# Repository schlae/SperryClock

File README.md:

# Nine Digit Sperry Neon Display Clock

Here's a cute little clock I designed that uses a Sperry neon display -- sometimes known as a Panaplex display. Please note this is not a fully completed project. Although I fabbed out boards and got the display working, I never got around to finishing the firmware.

The particular display in this clock is a Sperry SP-425-09, but the basic design will probably work with other Panaplex displays as well.

The brains of the operation is an ATMega328P with a 16MHz crystal. You can load it with the Arduino bootloader and write programs for it using the Arduino IDE, or you can program it directly using avr-gcc, AVR Libc, and avrdude.

[Here is the schematic.](https://github.com/schlae/SperryClock/blob/main/NineDigit.pdf)

The basic design uses 9 transistors to multiplex the segment signals to each of the digits in the display. Typical Panaplex displays must be multiplexed otherwise the segment cathode material will start to plate out and darken the display, so avoid operating the display with just a single digit turned on continuously.

The [firmware](https://github.com/schlae/SperryClock/blob/main/NineDigit.ino) is incomplete but does include all the code required to drive the multiplexed display.

Still to be done:

* Driver for the DS3231
* Button handling
* Clock logic 

## Fabrication and Assembly Notes
This is a two-layer board, outer dimensions of 115mm x 50mm. 

The Sperry display should be installed in a socket. I've specified a part from EDAC but you might be able to find a cheaper one. The pin spacing is 0.156" (3.96mm).

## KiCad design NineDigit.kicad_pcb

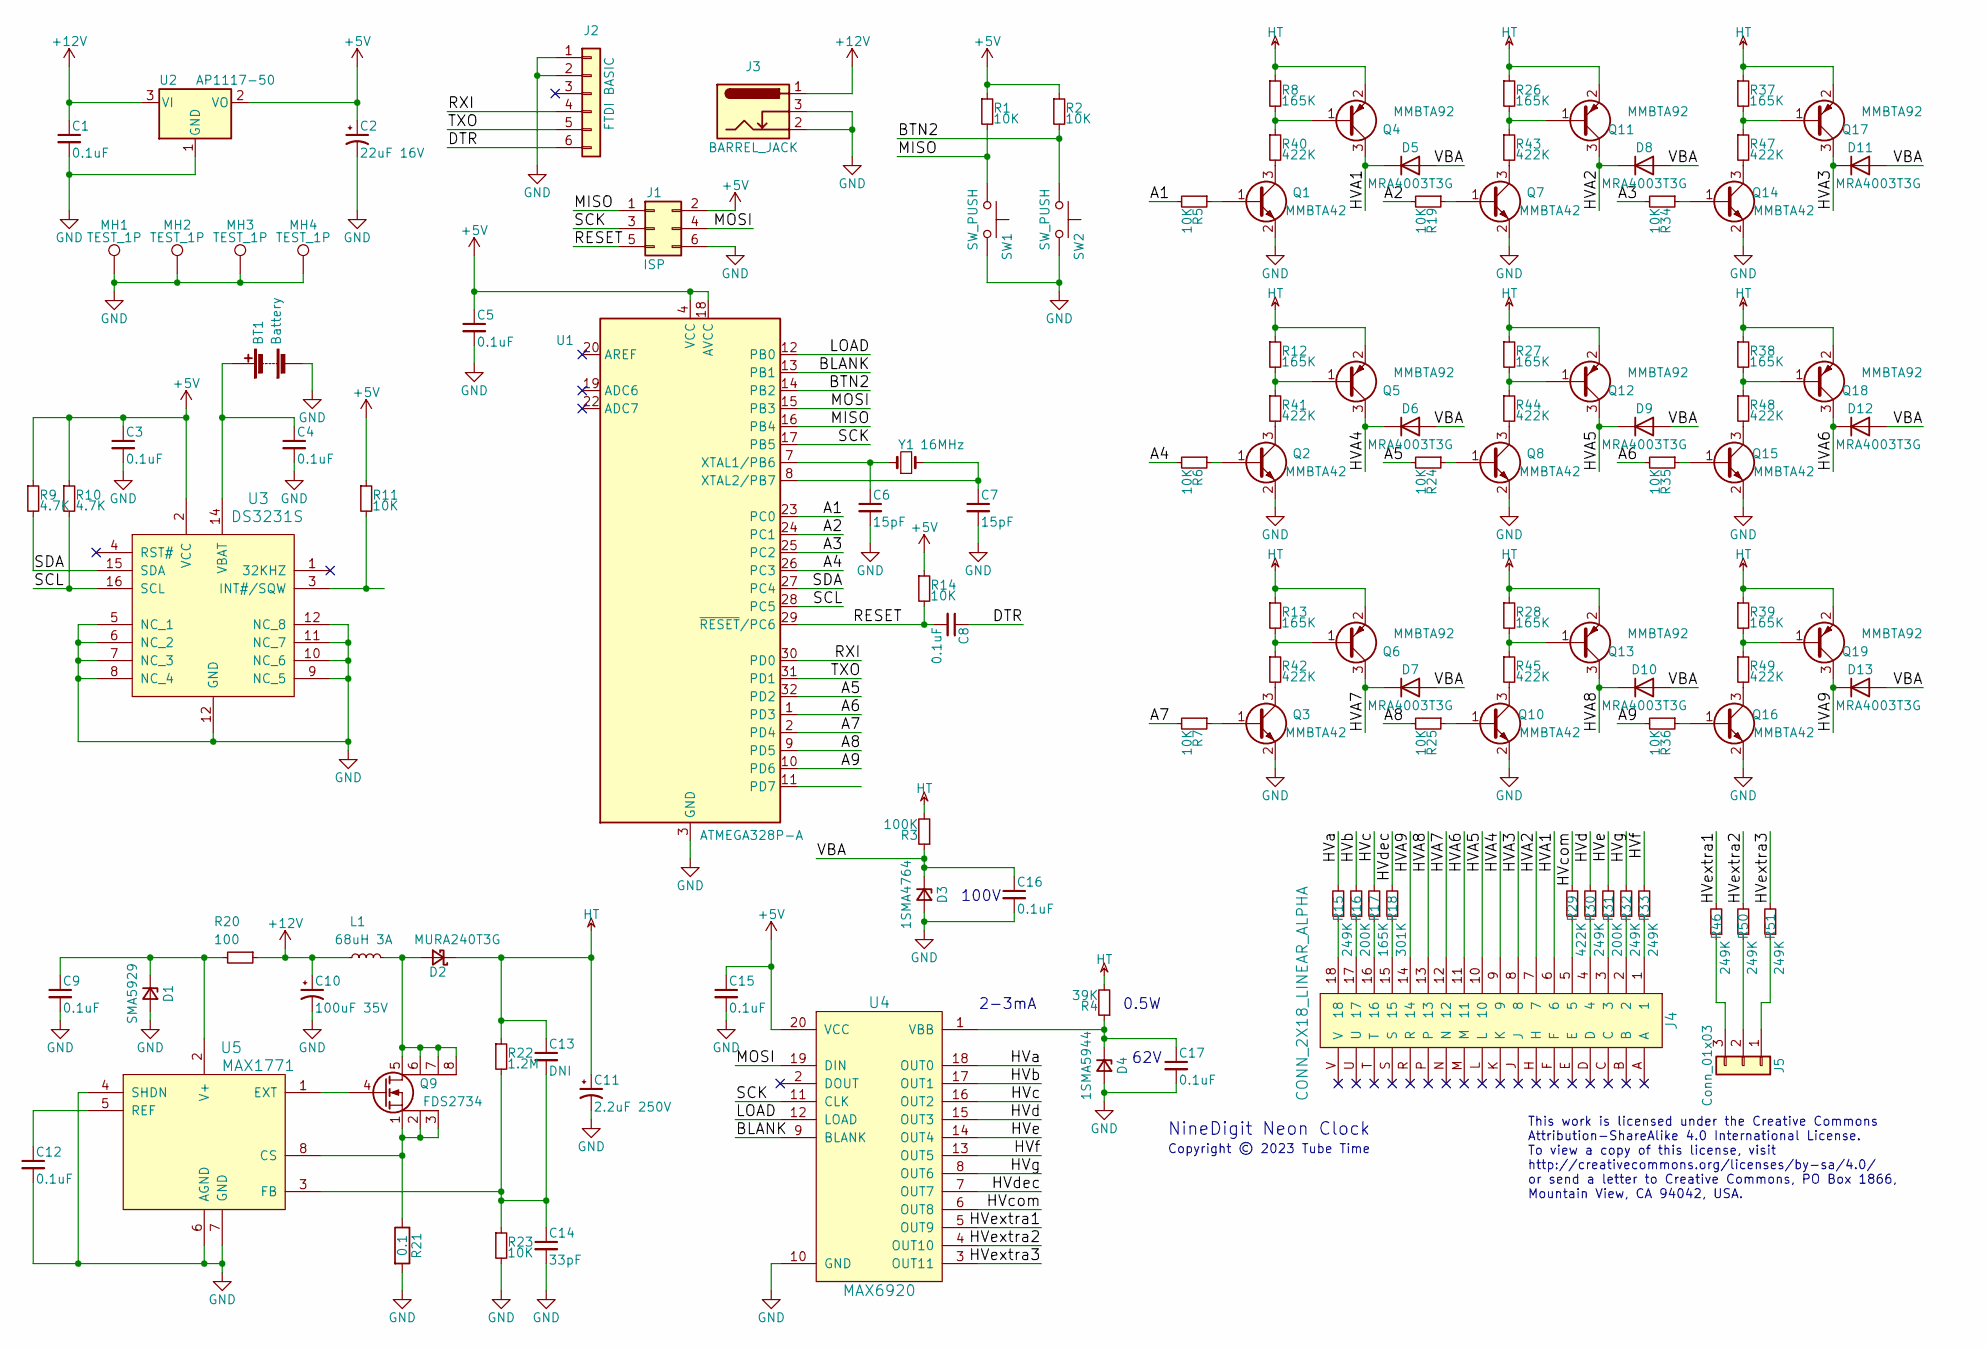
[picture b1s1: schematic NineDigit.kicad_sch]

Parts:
BT1: Battery; CR2032H
C1, C3, C4, C5, C8, C9, C12, C15: 0.1uF; CAPC1608X100
C2: 22uF 16V; CAPAE250P630X1100
C6, C7: 15pF; CAPC1608X100
C10: 100uF 35V; CAPAE250P630X1100
C11: 2.2uF 250V; CAPAE250P630X1100; MFG_PN 647-ULD2E2R2MED1TD
C13: DNI; CAPC2012X55
C14: 33pF; CAPC1608X100
C16, C17: 0.1uF; CAPC3225X110; Mouser 710-885342208004
D1: SMA5929; DIOM5226X210; Mouser 821-1SMA5929R3
D2: MURA240T3G; DIOM5226X210; Mouser 863-MURA240T3G
D3: 1SMA4764; DIOM5226X210; Mouser 821-1SMA4764R3
D4: 1SMA5944; DIOM5226X210; Mouser 821-1SMA5944R3
D5, D6, D7, D8, D9, D10, D11, D12, D13: MRA4003T3G; DIOM5226X210
J1: ISP; Pin_Header_Straight_2x03_Pitch2.54mm_SMD
J2: FTDI BASIC; Pin_Header_Straight_1x06_Pitch2.54mm
J3: BARREL_JACK; BarrelJack_Horizontal
J4: CONN_2X18_LINEAR_ALPHA; EDAC_357-036-520-208
J5: Conn_01x03; Pin_Header_Straight_1x03_Pitch2.54mm
L1: 68uH 3A; INDM125125X600; MFG_PN 652-SRR1260A-680M
MH1, MH2, MH3, MH4: TEST_1P; MountingHole_3.2mm_M3_Pad
Q1, Q2, Q3, Q7, Q8, Q10, Q14, Q15, Q16: MMBTA42; SOT95P230X117-3
Q4, Q5, Q6, Q11, Q12, Q13, Q17, Q18, Q19: MMBTA92; SOT95P230X117-3
Q9: FDS2734; SOP127P620X175-8; Mouser 512-FDS2734
R1, R2, R5, R6, R7, R11, R14, R19, R23, R24, R25, R34, R35, R36: 10K; RESC1608X55
R3: 100K; RESC3216X70
R4: 39K; RESC3216X70
R8, R12, R13, R17, R26, R27, R28, R37, R38, R39: 165K; RESC3216X70; Mouser 71-CRCW1206-165K-E3
R9, R10: 4.7K; RESC1608X55
R15, R30, R32, R33, R46, R50, R51: 249K; RESC3216X70; Mouser 71-CRCW1206-249K-E3
R16, R31: 200K; RESC3216X70; Mouser 71-CRCW1206-200K-E3
R18: 301K; RESC3216X70; Mouser 71-CRCW1206-301K-E3
R20: 100; RESC2012X55
R21: 0.1; RESC2012X55; Mouser 660-UR73V2ATTDR100F
R22: 1.2M; RESC3216X70; Mouser 660-HV732BTTD1204F
R29, R40, R41, R42, R43, R44, R45, R47, R48, R49: 422K; RESC3216X70; Mouser 71-CRCW1206-422K-E3
SW1, SW2: SW_PUSH; SW_PUSH_6mm
U1: ATMEGA328P-A; TQFP80P900X900X120-32
U2: AP1117-50; SOT230P700X170-3
U3: DS3231S; SOP127P1065X265-16
U4: MAX6920; SOP127P1065X265-20; Mouser 700-MAX6920AWP
U5: MAX1771; SOP127P620X175-8
Y1: 16MHz; XTAL500X320X120-2

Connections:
+5V: C2.1, C3.1, C5.1, C15.1, J1.2, R1.1, R2.1, R9.1, R10.1, R11.1, R14.1, U1.4 (VCC), U1.6 (VCC), U1.18 (AVCC), U2.2 (VO), U3.2 (VCC), U4.20 (VCC)
+12V: C1.1, C10.1, J3.1, L1.1, R20.1, U2.3 (VI)
/A1: R5.2, U1.23 (PC0)
/A2: R19.2, U1.24 (PC1)
/A3: R34.2, U1.25 (PC2)
/A4: R6.2, U1.26 (PC3)
/A5: R24.2, U1.32 (PD2)
/A6: R35.2, U1.1 (PD3)
/A7: R7.2, U1.2 (PD4)
/A8: R25.2, U1.9 (PD5)
/A9: R36.2, U1.10 (PD6)
/BLANK: U1.13 (PB1), U4.9 (BLANK)
/BTN2: R2.2, SW2.1, U1.14 (PB2)
/DTR: C8.1, J2.6
/HVA1: D5.1 (K), J4.6, Q4.3 (C)
/HVA2: D8.1 (K), J4.7, Q11.3 (C)
/HVA3: D11.1 (K), J4.8, Q17.3 (C)
/HVA4: D6.1 (K), J4.9, Q5.3 (C)
/HVA5: D9.1 (K), J4.10, Q12.3 (C)
/HVA6: D12.1 (K), J4.11, Q18.3 (C)
/HVA7: D7.1 (K), J4.12, Q6.3 (C)
/HVA8: D10.1 (K), J4.13, Q13.3 (C)
/HVA9: D13.1 (K), J4.14, Q19.3 (C)
/HVa: R15.2, U4.18 (OUT0)
/HVb: R16.2, U4.17 (OUT1)
/HVc: R17.2, U4.16 (OUT2)
/HVcom: R29.2, U4.6 (OUT8)
/HVd: R30.2, U4.15 (OUT3)
/HVdec: R18.2, U4.7 (OUT7)
/HVe: R31.2, U4.14 (OUT4)
/HVextra1: R46.2, U4.5 (OUT9)
/HVextra2: R50.2, U4.4 (OUT10)
/HVextra3: R51.2, U4.3 (OUT11)
/HVf: R33.2, U4.13 (OUT5)
/HVg: R32.2, U4.8 (OUT6)
/LOAD: U1.12 (PB0), U4.12 (LOAD)
/MISO: J1.1, R1.2, SW1.1, U1.16 (PB4)
/MOSI: J1.4, U1.15 (PB3), U4.19 (DIN)
/RESET: C8.2, J1.5, R14.2, U1.29 (~RESET/PC6)
/RXI: J2.4, U1.30 (PD0)
/SCK: J1.3, U1.17 (PB5), U4.11 (CLK)
/SCL: R10.2, U1.28 (PC5), U3.16 (SCL)
/SDA: R9.2, U1.27 (PC4), U3.15 (SDA)
/TXO: J2.5, U1.31 (PD1)
/VBA: C16.1, D3.1 (K), D5.2 (A), D6.2 (A), D7.2 (A), D8.2 (A), D9.2 (A), D10.2 (A), D11.2 (A), D12.2 (A), D13.2 (A), R3.1
GND: BT1.2 (-), C1.2, C2.2, C3.2, C4.2, C5.2, C6.2, C7.2, C9.2, C10.2, C11.2, C12.2, C14.2, C15.2, C16.2, C17.2, D1.2 (A), D3.2 (A), D4.2 (A), J1.6, J2.1, J2.2, J3.2, J3.3, MH1.1, MH2.1, MH3.1, MH4.1, Q1.2 (E), Q2.2 (E), Q3.2 (E), Q7.2 (E), Q8.2 (E), Q10.2 (E), Q14.2 (E), Q15.2 (E), Q16.2 (E), R21.2, R23.2, SW1.2, SW2.2, U1.3 (GND), U1.5 (GND), U1.21 (GND), U2.1 (GND), U3.5 (NC_1), U3.6 (NC_2), U3.7 (NC_3), U3.8 (NC_4), U3.9 (NC_5), U3.10 (NC_6), U3.11 (NC_7), U3.12 (GND), U4.10 (GND), U5.4 (SHDN), U5.6 (AGND), U5.7 (GND)
HT: C11.1, C13.1, D2.1 (K), Q4.2 (E), Q5.2 (E), Q6.2 (E), Q11.2 (E), Q12.2 (E), Q13.2 (E), Q17.2 (E), Q18.2 (E), Q19.2 (E), R3.2, R4.2, R8.1, R12.1, R13.1, R22.1, R26.1, R27.1, R28.1, R37.1, R38.1, R39.1
unnamed: BT1.1 (+), C4.1, U3.14 (VBAT)
unnamed: C6.1, U1.7 (XTAL1/PB6), Y1.1
unnamed: C7.1, U1.8 (XTAL2/PB7), Y1.2
unnamed: C9.1, D1.1 (K), R20.2, U5.2 (V+)
unnamed: C12.1, U5.5 (REF)
unnamed: C13.2, C14.1, R22.2, R23.1, U5.3 (FB)
unnamed: C17.1, D4.1 (K), R4.1, U4.1 (VBB)
unnamed: D2.2 (A), L1.2, Q9.5 (D1), Q9.6 (D2), Q9.7 (D3), Q9.8 (D4)
unnamed: J4.1, R33.1
unnamed: J4.2, R32.1
unnamed: J4.3, R31.1
unnamed: J4.4, R30.1
unnamed: J4.5, R29.1
unnamed: J4.15, R18.1
unnamed: J4.16, R17.1
unnamed: J4.17, R16.1
unnamed: J4.18, R15.1
unnamed: J5.1, R51.1
unnamed: J5.2, R50.1
unnamed: J5.3, R46.1
unnamed: Q1.1 (B), R5.1
unnamed: Q1.3 (C), R40.2
unnamed: Q2.1 (B), R6.1
unnamed: Q2.3 (C), R41.2
unnamed: Q3.1 (B), R7.1
unnamed: Q3.3 (C), R42.2
unnamed: Q4.1 (B), R8.2, R40.1
unnamed: Q5.1 (B), R12.2, R41.1
unnamed: Q6.1 (B), R13.2, R42.1
unnamed: Q7.1 (B), R19.1
unnamed: Q7.3 (C), R43.2
unnamed: Q8.1 (B), R24.1
unnamed: Q8.3 (C), R44.2
unnamed: Q9.1 (S1), Q9.2 (S2), Q9.3 (S3), R21.1, U5.8 (CS)
unnamed: Q9.4 (G), U5.1 (EXT)
unnamed: Q10.1 (B), R25.1
unnamed: Q10.3 (C), R45.2
unnamed: Q11.1 (B), R26.2, R43.1
unnamed: Q12.1 (B), R27.2, R44.1
unnamed: Q13.1 (B), R28.2, R45.1
unnamed: Q14.1 (B), R34.1
unnamed: Q14.3 (C), R47.2
unnamed: Q15.1 (B), R35.1
unnamed: Q15.3 (C), R48.2
unnamed: Q16.1 (B), R36.1
unnamed: Q16.3 (C), R49.2
unnamed: Q17.1 (B), R37.2, R47.1
unnamed: Q18.1 (B), R38.2, R48.1
unnamed: Q19.1 (B), R39.2, R49.1
unnamed: R11.2, U3.3 (INT#/SQW)

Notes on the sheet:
This work is licensed under the Creative Commons Attribution-ShareAlike 4.0 International License. To view a copy of this license, visit http://creativecommons.org/licenses/by-sa/4.0/ or send a letter to Creative Commons, PO Box 1866, Mountain View, CA 94042, USA.
0.5W
2-3mA
62V
NineDigit Neon Clock
100V
Copyright © 2023 Tube Time

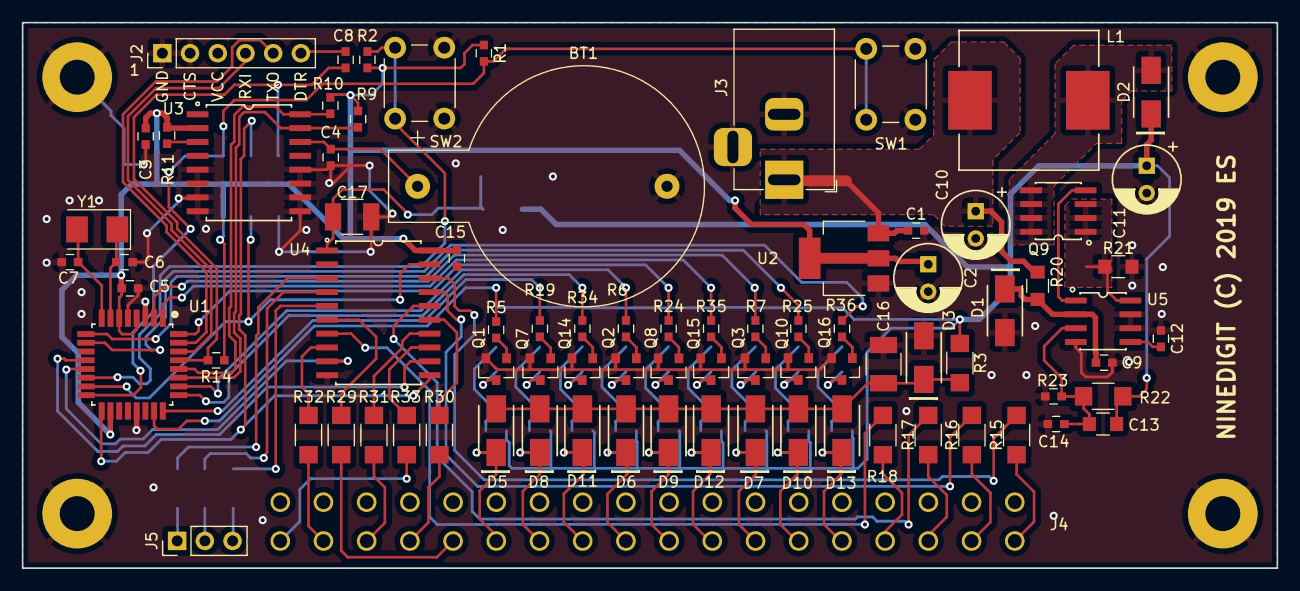
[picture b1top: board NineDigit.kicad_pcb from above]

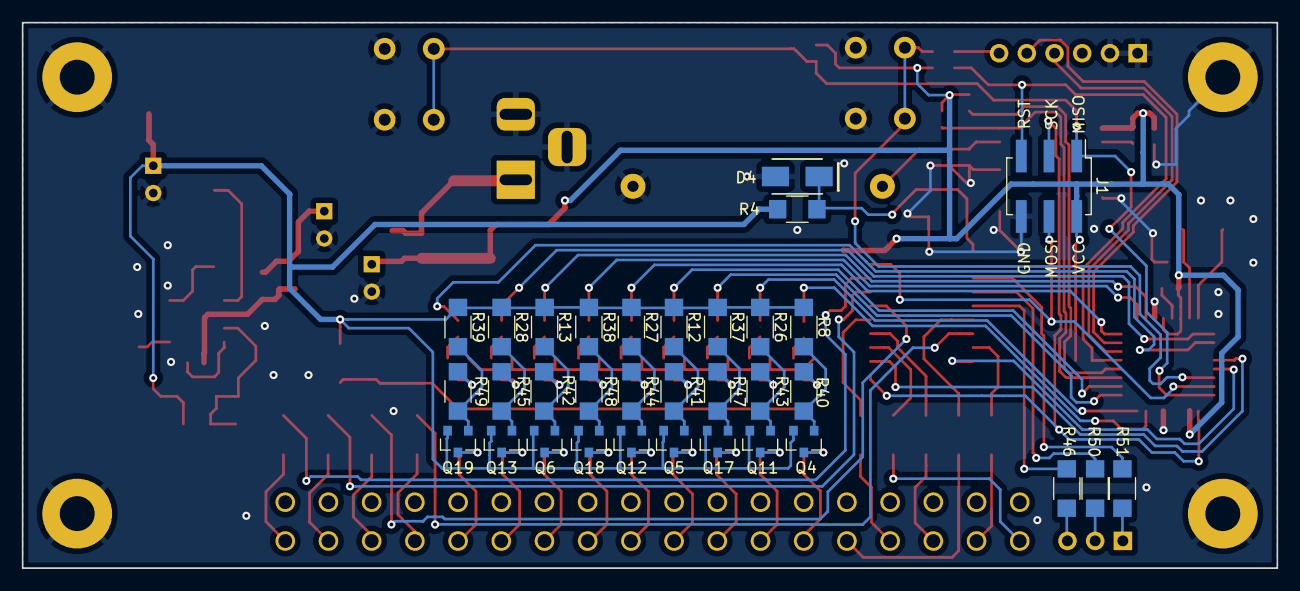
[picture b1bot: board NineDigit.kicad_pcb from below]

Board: 2 copper layers, 115.0 x 50.0 mm, 119 parts (33 on the bottom side), 97 nets.

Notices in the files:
NineDigit.kicad_pcb:
Copyright (C) 2023 Tube Time
NINEDIGIT (C) 2019 ES
